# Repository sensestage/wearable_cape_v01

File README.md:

# wearable_cape_v01

First version of a wearable cape for the VanAbbemuseum Earthquake Archive

## ToDos

### Minor fixes for v02

- fix wiring errors on minijack outputs to amplifiers
- Swap out the buffered voltage divider 1.8V reference for a fixed regulator
- Add bypass capacitors to the active filters
- widen power rail traces to the amplifier boards
- silkscreen labels for switch functionality and outputs
- breakout capability of mode switch, reset switch, & status LEDs
  - user leds, see: http://beaglebone.cameon.net/home/using-the-user-leds

### Larger improvements

- add additional 2-channel output for full access to all output channels

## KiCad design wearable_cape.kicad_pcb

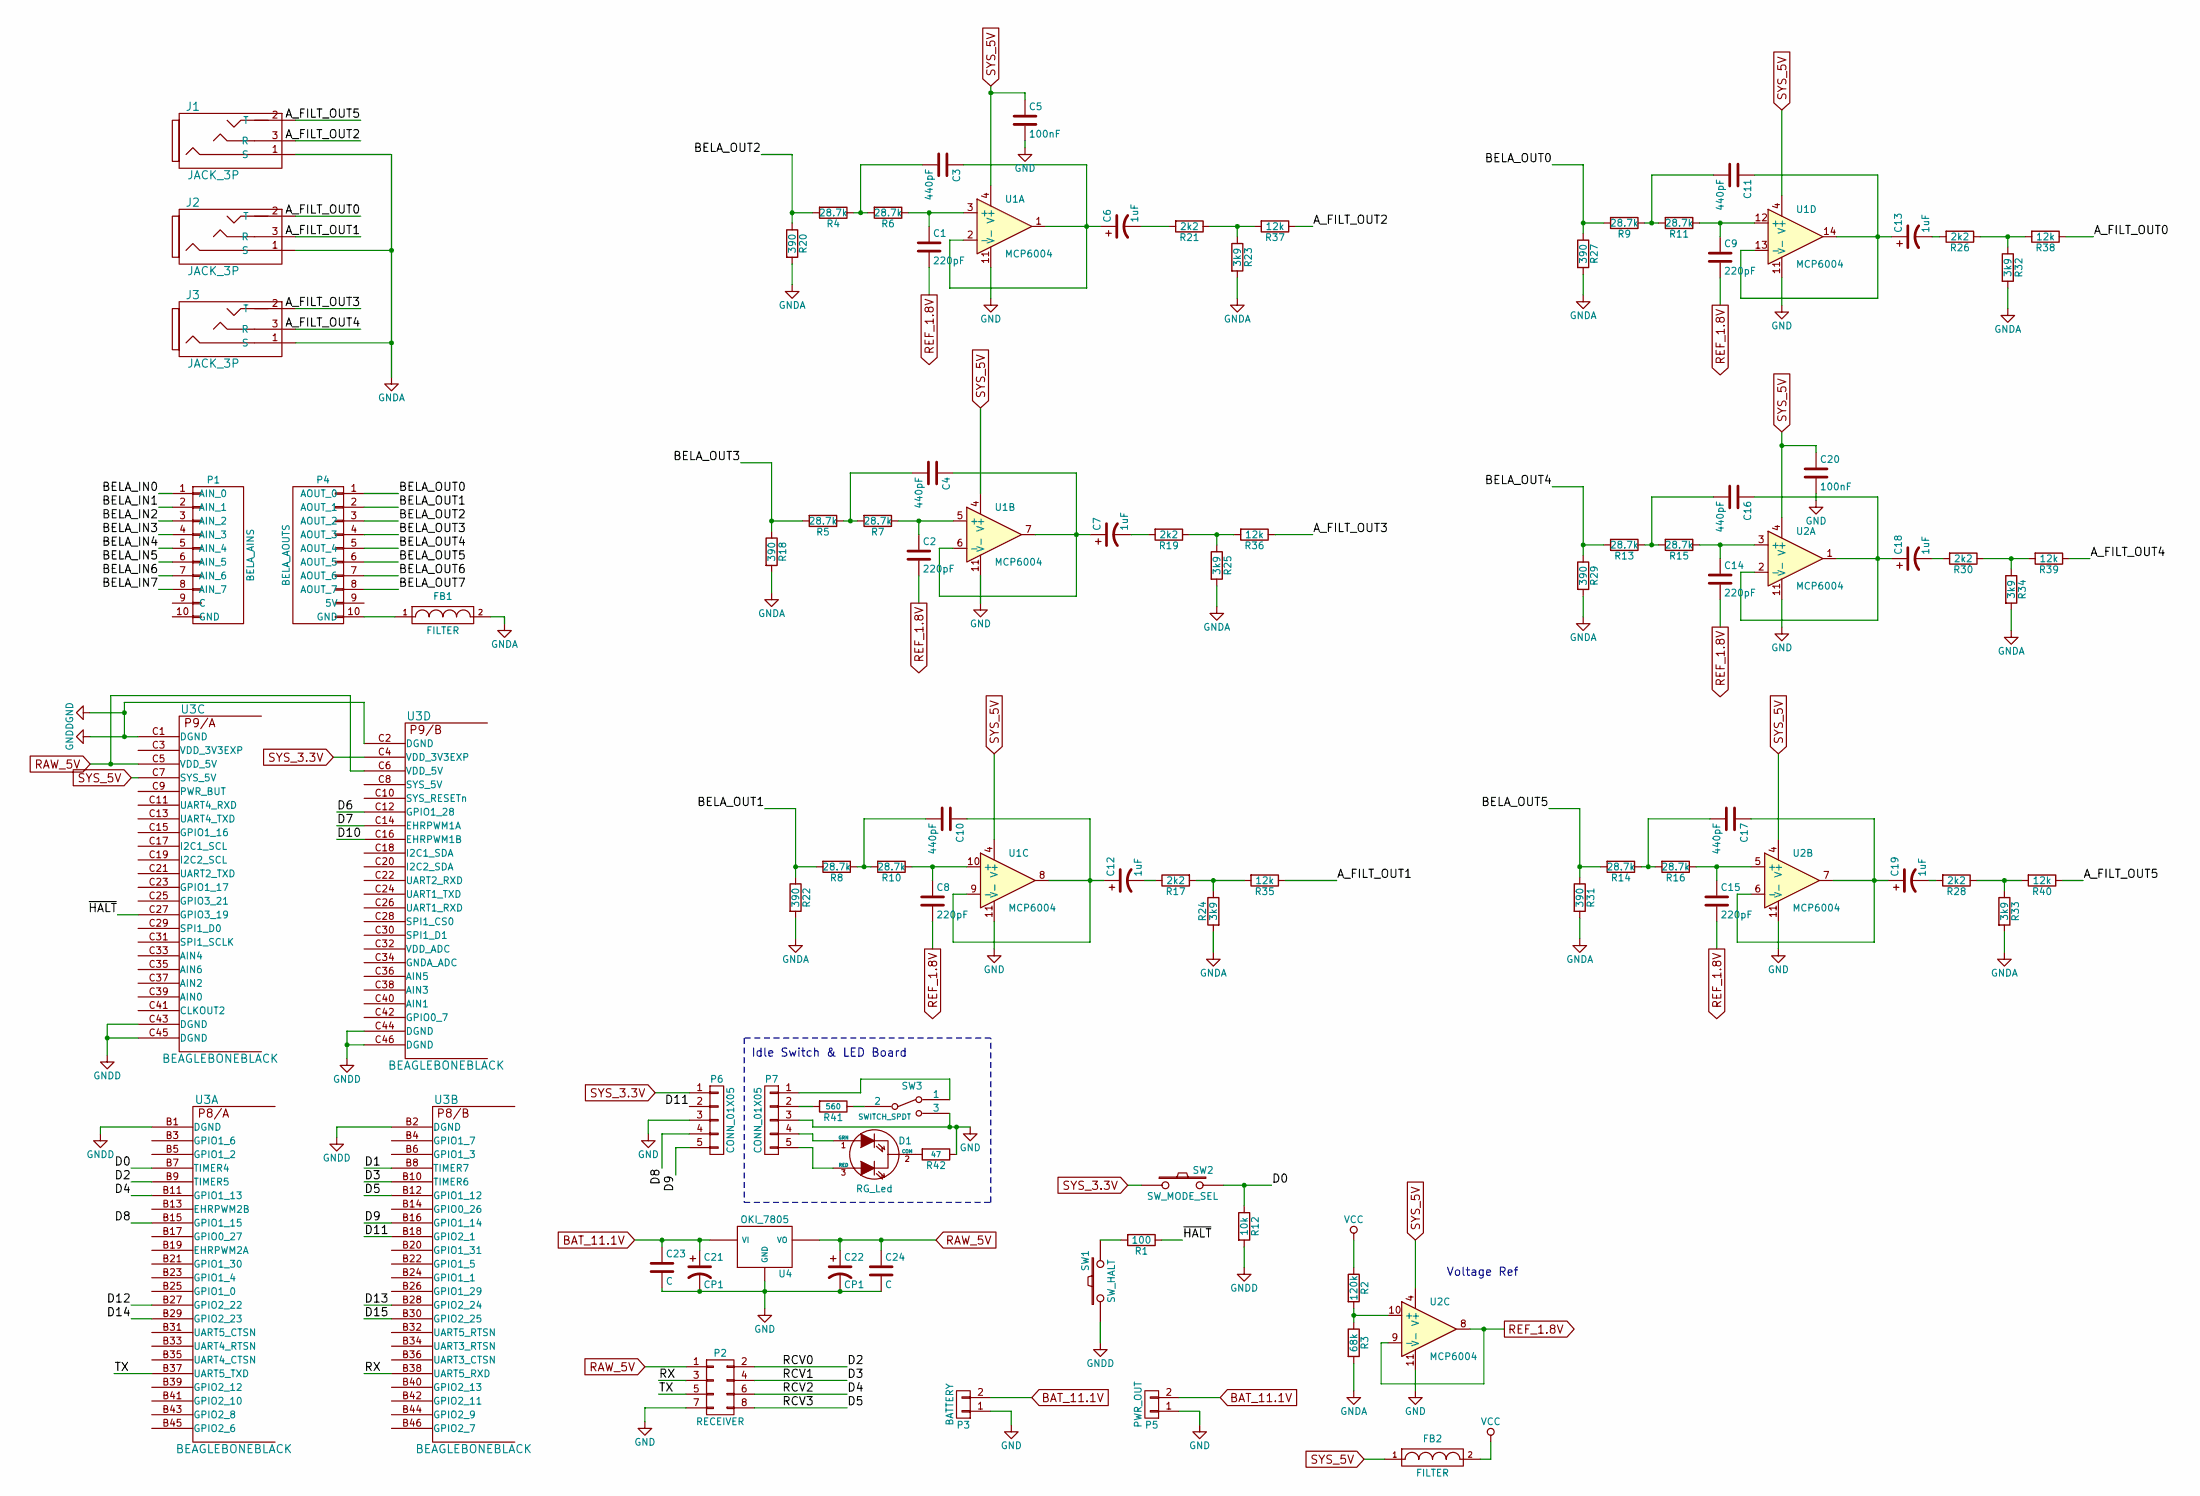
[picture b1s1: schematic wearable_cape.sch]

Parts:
C1, C2, C8, C9, C14, C15: 220pF; C_0603_HandSoldering
C3, C4, C10, C11, C16, C17: 440pF; C_0603_HandSoldering
C5, C20: 100nF; C_0603_HandSoldering
C6, C7, C12, C13, C18, C19: 1uF; SMD-1206_Pol
C21, C22: CP1; SMD-1210_Pol
C23, C24: C; C_0603_HandSoldering
D1: RG_Led
FB1, FB2: FILTER; R_0603_HandSoldering
J1, J2, J3: JACK_3P; Lumberg_1503_03
P1: BELA_AINS; Pin_Header_Straight_1x10
P2: RECEIVER; IDC_Header_Straight_10pins
P3: BATTERY; TerminalBlock_Pheonix_PT-3.5mm_2pol
P4: BELA_AOUTS; Pin_Header_Straight_1x10
P5: PWR_OUT; TerminalBlock_Pheonix_MPT-2.54mm_2pol
P6, P7: CONN_01X05
R1: 100; R_0603_HandSoldering
R2: 120k; R_0603_HandSoldering
R3: 68k; R_0603_HandSoldering
R4, R5, R6, R7, R8, R9, R10, R11, R13, R14, R15, R16: 28.7k; R_0603_HandSoldering
R12: 10k; R_0603_HandSoldering
R17, R19, R21, R26, R28, R30: 2k2; R_0603_HandSoldering
R18, R20, R22, R27, R29, R31: 390; R_0603_HandSoldering
R23, R24, R25, R32, R33, R34: 3k9; R_0603_HandSoldering
R35, R36, R37, R38, R39, R40: 12k; R_0603_HandSoldering
R41: 560
R42: 47
SW1: SW_HALT; SW_SPST_EVQPE1
SW2: SW_MODE_SEL; SW_SPST_EVQPE1
SW3: SWITCH_SPDT
U1, U2: MCP6004; SOIC-14_3.9x8.7mm_Pitch1.27mm
U3: BEAGLEBONEBLACK; beagleboneblack_nomount
U4: OKI_7805; Socket_Strip_Angled_1x03

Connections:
/A_FILT_OUT0: J2.2 (T), R38.1
/A_FILT_OUT1: J2.3 (R), R35.1
/A_FILT_OUT2: J1.3 (R), R37.1
/A_FILT_OUT3: J3.2 (T), R36.1
/A_FILT_OUT4: J3.3 (R), R39.1
/A_FILT_OUT5: J1.2 (T), R40.1
/BELA_IN0: P1.1 (AIN_0)
/BELA_IN1: P1.2 (AIN_1)
/BELA_IN2: P1.3 (AIN_2)
/BELA_IN3: P1.4 (AIN_3)
/BELA_IN4: P1.5 (AIN_4)
/BELA_IN5: P1.6 (AIN_5)
/BELA_IN6: P1.7 (AIN_6)
/BELA_IN7: P1.8 (AIN_7)
/BELA_OUT0: P4.1 (AOUT_0), R9.2, R27.1
/BELA_OUT1: P4.2 (AOUT_1), R8.2, R22.1
/BELA_OUT2: P4.3 (AOUT_2), R4.2, R20.1
/BELA_OUT3: P4.4 (AOUT_3), R5.2, R18.1
/BELA_OUT4: P4.5 (AOUT_4), R13.2, R29.1
/BELA_OUT5: P4.6 (AOUT_5), R14.2, R31.1
/BELA_OUT6: P4.7 (AOUT_6)
/BELA_OUT7: P4.8 (AOUT_7)
/D0: R12.1, SW2.2, U3.B7 (TIMER4)
/D1: U3.B8 (TIMER7)
/D2: P2.2, U3.B9 (TIMER5)
/D3: P2.4, U3.B10 (TIMER6)
/D4: P2.6, U3.B11 (GPIO1_13)
/D5: P2.8, U3.B12 (GPIO1_12)
/D6: U3.C12 (GPIO1_28)
/D7: U3.C14 (EHRPWM1A)
/D8: P6.4, U3.B15 (GPIO1_15)
/D9: P6.5, U3.B16 (GPIO1_14)
/D10: U3.C16 (EHRPWM1B)
/D11: P6.2, U3.B18 (GPIO2_1)
/D12: U3.B27 (GPIO2_22)
/D13: U3.B28 (GPIO2_24)
/D14: U3.B29 (GPIO2_23)
/D15: U3.B30 (GPIO2_25)
/RX: P2.3, U3.B38 (UART5_RXD)
/TX: P2.5, U3.B37 (UART5_TXD)
/~HALT: R1.1, U3.C27 (GPIO3_19)
BAT_11.1V: C21.1, C23.1, P3.2, P5.2, U4.1 (VI)
GND: C5.2, C20.2, C21.2, C22.2, C23.2, C24.2, P2.7, P3.1, P5.1, P6.3, P7.3, R12.2, R42.1, SW1.1, SW3.3, U1.11 (V-), U2.11 (V-), U3.B1 (DGND), U3.B2 (DGND), U3.C1 (DGND), U3.C2 (DGND), U3.C43 (DGND), U3.C44 (DGND), U3.C45 (DGND), U3.C46 (DGND), U4.2 (GND)
GNDA: FB1.2, J1.1 (S), J2.1 (S), J3.1 (S), R3.2, R18.2, R20.2, R22.2, R23.2, R24.2, R25.2, R27.2, R29.2, R31.2, R32.2, R33.2, R34.2
unnamed: C1.1, R6.1, U1.3 (+)
unnamed: C2.1, R7.1, U1.5 (+)
unnamed: C3.1, C6.1, U1.1, U1.2 (-)
unnamed: C3.2, R4.1, R6.2
unnamed: C4.1, C7.1, U1.6 (-), U1.7
unnamed: C4.2, R5.1, R7.2
unnamed: C6.2, R21.2
unnamed: C7.2, R19.2
unnamed: C8.1, R10.1, U1.10 (+)
unnamed: C9.1, R11.1, U1.12 (+)
unnamed: C10.1, C12.1, U1.8, U1.9 (-)
unnamed: C10.2, R8.1, R10.2
unnamed: C11.1, C13.1, U1.13 (-), U1.14
unnamed: C11.2, R9.1, R11.2
unnamed: C12.2, R17.1
unnamed: C13.2, R26.2
unnamed: C14.1, R15.1, U2.3 (+)
unnamed: C15.1, R16.1, U2.5 (+)
unnamed: C16.1, C18.1, U2.1, U2.2 (-)
unnamed: C16.2, R13.1, R15.2
unnamed: C17.1, C19.1, U2.6 (-), U2.7
unnamed: C17.2, R14.1, R16.2
unnamed: C18.2, R30.2
unnamed: C19.2, R28.2
unnamed: D1.1 (GRN), P7.4
unnamed: D1.2 (COM), R42.2
unnamed: D1.3 (RED), P7.5
unnamed: FB1.1, P4.10 (GND)
unnamed: P7.1, SW3.1
unnamed: P7.2, R41.2
unnamed: R1.2, SW1.2
unnamed: R2.2, R3.1, U2.10 (+)
unnamed: R17.2, R24.1, R35.2
unnamed: R19.1, R25.1, R36.2
unnamed: R21.1, R23.1, R37.2
unnamed: R26.1, R32.1, R38.2
unnamed: R28.1, R33.1, R40.2
unnamed: R30.1, R34.1, R39.2
unnamed: R41.1, SW3.2
RAW_5V: C22.1, C24.1, P2.1, U3.C5 (VDD_5V), U3.C6 (VDD_5V), U4.3 (VO)
REF_1.8V: C1.2, C2.2, C8.2, C9.2, C14.2, C15.2, U2.8, U2.9 (-)
SYS_3.3V: P6.1, SW2.1, U3.C4 (VDD_3V3EXP)
SYS_5V: C5.1, C20.1, FB2.1, U1.4 (V+), U2.4 (V+), U3.C7 (SYS_5V)
VCC: FB2.2, R2.1

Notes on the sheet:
Voltage Ref
Idle Switch & LED Board

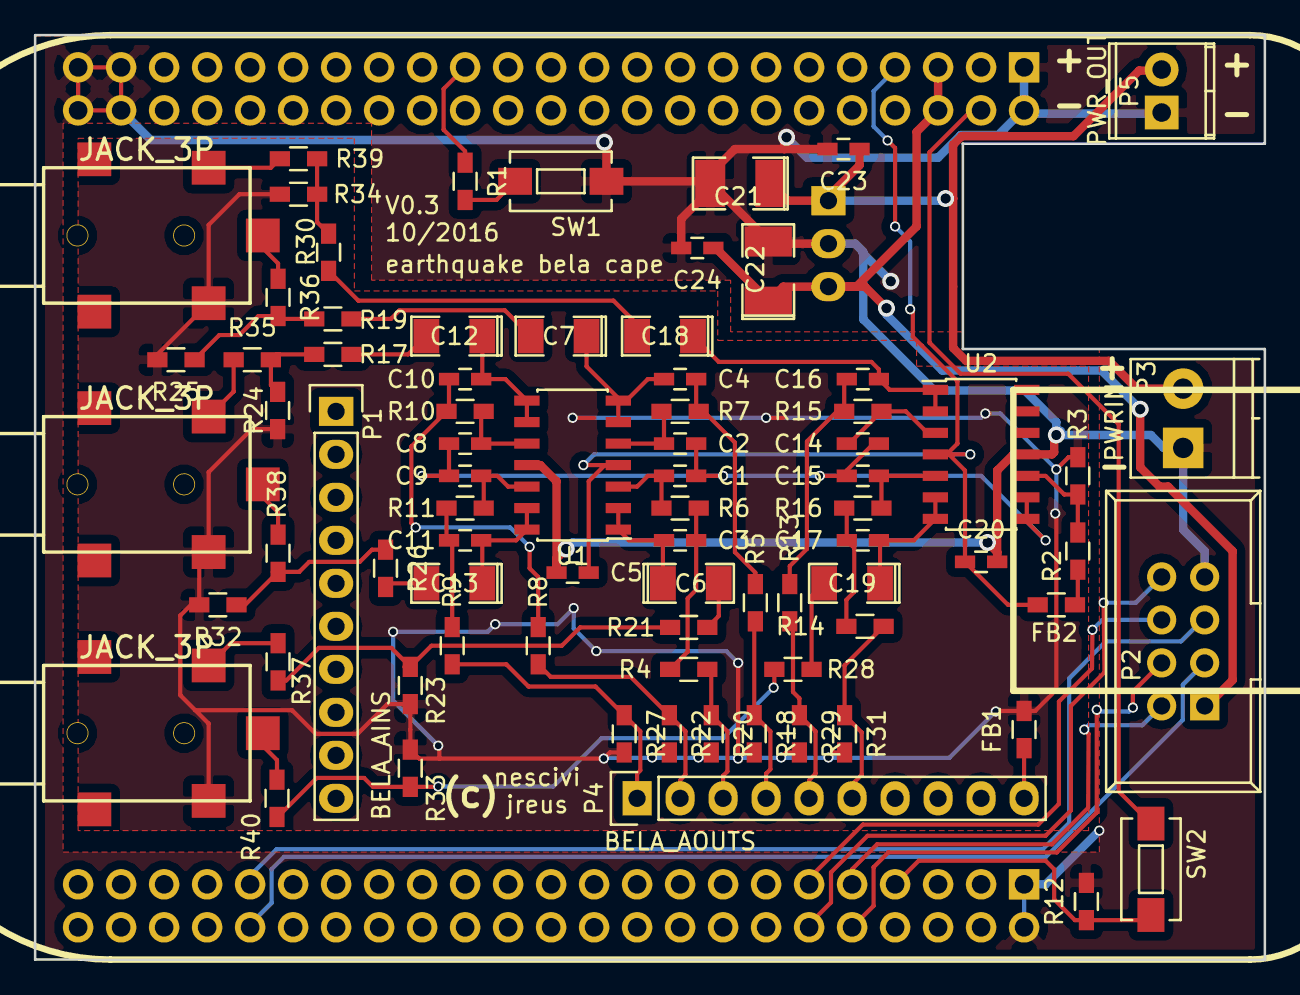
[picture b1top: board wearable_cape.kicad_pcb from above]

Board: 2 copper layers, 72.6 x 54.6 mm, 80 parts (1 on the bottom side), 61 nets.

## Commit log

2016-09-22 added new library components and beginning of schematic for filters and connectors
2016-10-04 schematic updates
2016-10-19 Updates to pcb: use beagleboneblack part in schematic, update the parts that did not have proper references, import all footprints to the pcb
2016-10-19 basic routing done
2016-10-19 added zones
2016-10-19 Updates to PCB and first BOM files
2016-10-19 Gerber files
2016-10-19 Fill in zones better
2016-10-20 created TODO.md
2016-10-20 added todo list to README.md
2016-10-20 merged todos into README.md
2016-10-20 updates to BOM
2016-10-20 added new simulations for attenuating filter
2016-10-20 added bode plot of new filter
2016-10-20 updates to pcb: add attenuation, add headphone jacks, fix power supply opamps
2016-10-20 Update gerber files with latest version of pcb
2016-10-20 small update to pcb, updates to BOM
2016-10-20 updated gerbers
2016-10-20 more updates to PCB
2016-10-20 update BOM
2016-10-20 add non plated holes gerber file
2016-10-20 updated simulation with transient analysis of latest filter design
2016-10-21 add ferrite beads, and fix GNDA -> 1.8_VREF
2016-10-21 updates to the BOM
2016-10-21 updates: footprint check, cutout for regulator, larger power input screw terminal
2016-10-21 kicad module for OKI regulator outline
2016-10-21 update of the gerber files; v0.2a; uploaded to EuroCircuits
2016-10-24 added several options for attenuation of circuit.
2016-10-24 gerbers for latest changes; version 0.3
2016-10-24 filter simulations for 3V peak2peak attenuation
2016-11-16 rename to .csv of bom list
2016-11-16 small updates to kicad project
2016-11-16 updates to BOM spreadsheet
2016-11-16 Make a note of which mistakes there were on v0.3 of the pcb
2016-12-13 gitignore
2016-12-13 removed OSX specific files
2017-03-06 renamed gerber folder to be board version specific
2017-03-06 version-specific gerbers folder
2017-03-06 reference pdfs for schematics & PCB
2017-03-06 fixed minijack connections in schematic
2018-02-24 added some documentation
2018-02-24 added MAX6100 1.8v reference datasheet & annotated PCB design
2018-02-28 put schematic in with the matching gerbers.
2018-02-28 fixed jack plugs pinout and made numbering of outputs consistent.
